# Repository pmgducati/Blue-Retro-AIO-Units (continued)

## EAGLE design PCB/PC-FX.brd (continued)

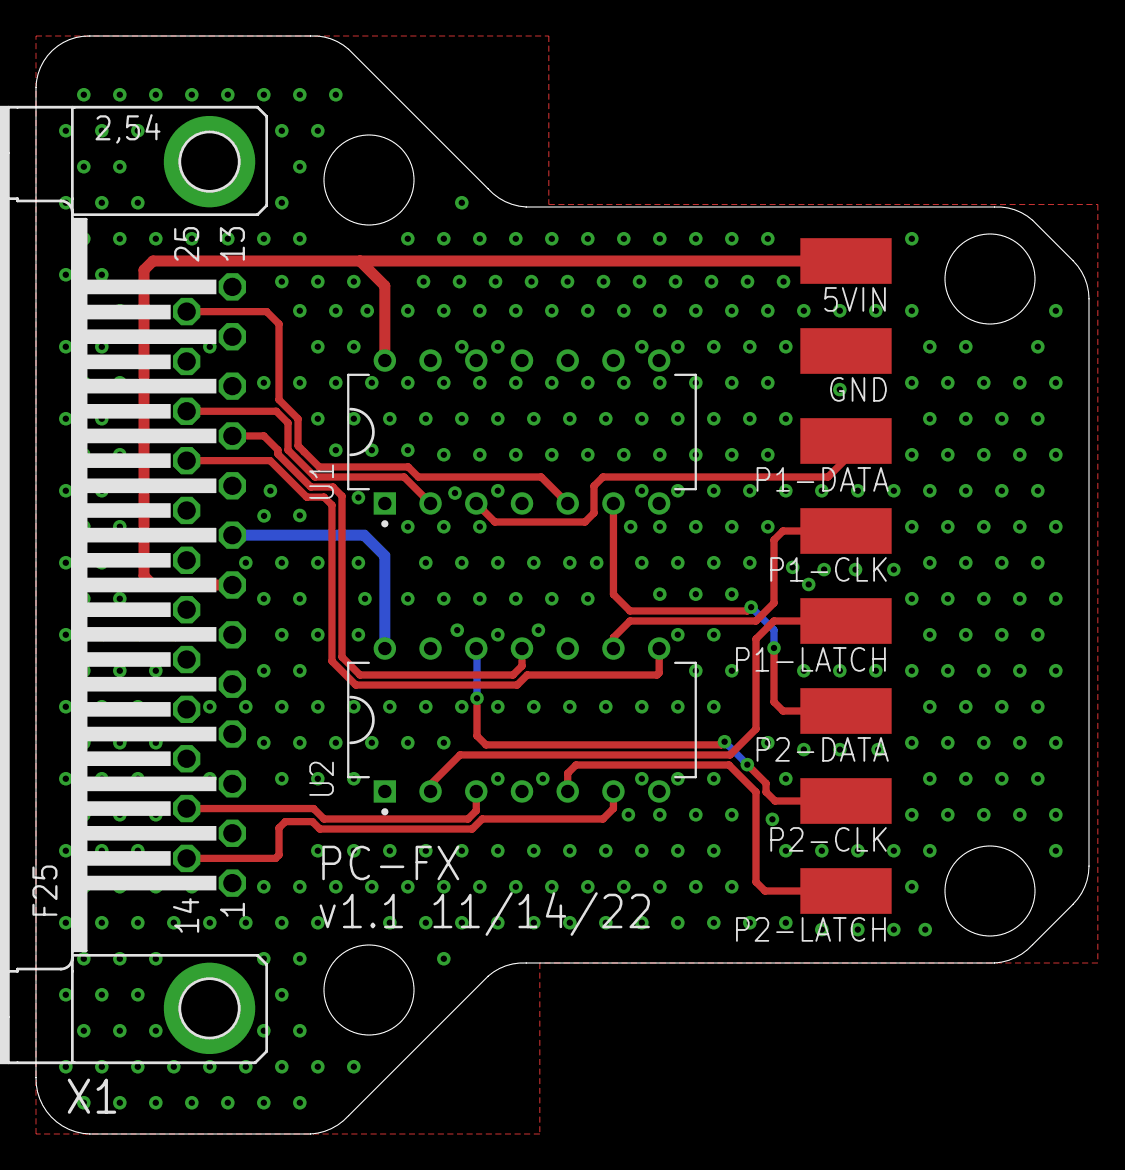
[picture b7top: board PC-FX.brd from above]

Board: 2 copper layers, 58.5 x 61.0 mm, 11 parts (0 on the bottom side), 15 nets.

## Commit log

2022-02-18 Initial Commit of all Files
2022-02-27 PCB Updates/New Additions
    All existing PCBs had silkscreen updates and NES, Virtual Boy, PSX/PS2, Nintendo 64, Saturn have been added.
2022-02-27 BOM Update
    Added extension Cable Links
2022-03-03 Clean Up
    Removing Uneeded Files
2022-03-03 Created Readme
2022-03-03 Clean Up Files
2022-03-14 Datasheets, BOM Update, 3 New PCBs
    Added Datasheets for the Female/Male DB25 connectors
    Updated formatting on the BOM
    New PCBs:
    Added Nintendo 64 (Updated to 1.1, Moved VIN from 5V to 3V3)
    Added Sega Saturn (Updated to 1.1, Added 5V and GND Pads on bottom for Second player pads to ease install)
    Added NES
2022-03-14 Working On Virtual Boy PCB
    Need to find/make a cable that is not prohibitively expensive to test.
2022-03-14 PCB for PSX/PS2
    Working on testing the PCB
2022-03-14 Housing for PCBs
    This will include the housing designs for the Main PCB and all Aux PCBs
2022-03-15 Housing Update
    Finishing housing shape, PCB Mounts, Venting, Branding and System Names. Snap fit and wire holes not started
2022-03-15 Controller Wire Holes and Player Markings
    Added Controller wire holes and player markings per system
2022-03-21 Preliminary CAD and STLs
    The CAD is finished and STL Created. I have ordered the Housings to make sure the snap fit will work as intended. Once I receive the housings and test them I will merge the branch if everything looks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
2022-03-21 BOM Update
    Updated ESP32 Link to model with correct footprint in BOM
2022-03-22 PS2 Power Pin Swap
    The PCB could not detect the correct system using the 8V from the PS2 to the 5VIN on the ESP. Moving to the 3V3 from the PS2 to 3V3IN on the ESP corrected the issue and the PCB not works as intended.
2022-03-23 Moving Files
    moved Flashing tool to Flashing Stuff Directory and added 1.4 FW from darthcloud
2022-03-23 Sharp Edge Fix for Shapeways
    The cutout for the DB25 connector on the top parts had a fillet applied to eliminate a sharp edge that would have caused printing problems.
2022-03-23 Updated Pad Name for 3V3 input
    Pad name was still listed as P1-4/P2-4 which is the 8V pin, The pads have been renamed and order updated on the PCB
2022-03-24 Power Pin addition
    After working with Darthcloud, it was revealed that some PS2 consoles have weak VIN on either the 8V or the 3V3. To make sure this PCB will work in either situation, I have added the 8V (Pad 3) pad b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
2022-04-02 PCB Update for better Housing Fit
    All the PCBs were updated for better housing fitment.
    Common Changes across all PCBs:
    1. All Aux PCBs are now the exact same size. (there was a .1mm-.5mm Variance previous)
    2. All Aux PCBs Mounting holes are in the same location (there was a .05mm-.1mm Variance previous)
    3. The DB25 has been moved 1.2mm close to the edge of the PCB for better connection when in the housing.
    PCB Specific Updates:
2022-04-02 Housing Update
    Widened the DB25 opening to allow male DB25 to fit over Female DB25 while in Housing, relocated PCB mounts to match PCB hole location in recent change.
2022-04-06 Added SNES PCB and Gerber
    Added SNES PCB and Gerber
2022-04-06 Add Dreamcast PCB and Gerber
    Add Dreamcast PCB and Gerber
2022-04-06 Removing Eagle Working Files
2022-04-06 Add NeoGeo PCBs
    Added Neogeo/Jamma/Supergun PCBs. Both OD and PP versions
2022-04-06 Add PC-FX
    Added PC-FX PCB Sch and Gerber
2022-04-06 Add CDi
    Added CDi PCB Schetmatic and gerber
2022-04-06 Add Jaguar
    Added Atari Jaguar PCB, Schematic and Gerber
2022-04-06 Add Sega Genesis
    Added Sega Genesis PCB, Schematic and Gerber
2022-04-06 Add Atari 2600 and SG-1000/SMS
    Added PCBs, Schematics and Gerbers for both PP and OD variants of the Atari 2600 and SG-1000/SMS (Both known as Parallel 2P)
2022-04-15 Housing Update and Font Add
    Changed female snap fit on the main housing bottom to overrun the main counterpart on both sides by .5mm (was 1mm)
    Updated STLs for Main Housing Bottom and all AUX Tops as this was not done on last commit.
    Added Font used for console logos
2022-04-15 Adding Project Status XLS
2022-04-16 TG-16
    Turbugrafx-16 Configuration is complete and Sega Genesis is in progress
2022-04-18 Added console variants to housing CAD and updated STLs
    Refreshed all Current STLs, Added 9 Variant AUX Covers to the Housing CAD
    New Variants Tops:
    Atari 2600, Atari 7800, Phillips CD-i, Famicom, Sega Genesis, Super Famicom, SNES, TurboGrafx 16 and Virtual Boy
2022-04-19 Added New Systems Housing Variants and supporting fonts
    Finished Housing Variants for Atari Jaguar, Dreamcast, Neo Geo, PC-FX, Sega Master System, Sega Mega Drive and SG-1000
    Gerbers for all files have been created and fonts used added to the fonts folder.
2022-04-19 Changed Player Order for N64 and Gamecube
    Reversed the player order of the pads on the PCB, when installing in the housing the controller wires would twist. this resolves that issue.
2022-04-20 Added Atari 7800 PCB and Gerber
    PCB was successfully able to be in the same footprint as all other variants. However it is the tightest design of all variants!
2022-04-20 Updated Project Status XLS
2022-04-20 Added Sega Genesis/Megadrive Multitap Support
    Added PCB/Gerber and Update SW CAD/ Added STLs for the Genesis/Megadrive Multitap version.
2022-04-20 JVS PCB
    Working on JVS PCB, need some clarification from Darthcloud on the Schematic Labels before proceeding
2022-04-27 BOM Update
    Updated BOM to include all recently added System components
2022-05-03 Naming Cleanup
    Changed Naming to be consistent between repos
2022-06-08 Fixed Omission of Main PCB in BOME PDF
    The print area was not correct in the XLS which then omitted the Main PCB. It has been updated.
2022-06-14 Update Project Status
    PC-FX functionality is confirmed, thanks to hipsofjw for testing it for me.
2022-06-14 CD-i PCB/BOM Update
    Identified USB Mini from Digikey and add it to the BOM.
    Updated the PCB to match the layout for the USB Mini Connector and added a callout on the PCB that the connector is required for 5V Power.
    Updated project status to include the complete PC-FX Status.
2022-06-14 Update BOM.pdf
    Added CD-i USB Mini connector
2022-06-15 CD-i Housing Update
    Added a opening in the housing for the usb power port and offset the controller cable hole to the side. Includes the solidworks files and STLs
2022-06-15 Adding P2 Controller Wire hole to Housing
2022-07-01 Adding Alternate Main PCB
    I added a alternate Main PCB that has a more standard (wider) ESP foorprint.
    The BOM has also been updated to include the Main ALT PCB
2022-07-01 Create Main - Wide ESP_2022-07-01.zip
    Forgot to add gerber for the alternate Main PCB in the last merge
2022-09-12 Updates from Issues 42/43/18
    Closed Issues 42 and 43 as Sega Genesis and PSX have been successfully tested and functional.
    Updated Dreamcast PCB per comment in Issue 18 - Reversed P1-P4 pads to match housing
    Updated Project Status to reflect #42 and #43 Complete
2022-09-12 Update README.md
    Updated Project Status
2022-11-14 Added exposed GND plane at DB25 anchors
    All PCBs have been update to have exposed GND plane pads for the DB25 anchor points.
    This resolves Issue 54
2022-11-14 Update BOM.xlsx
    Changed the Link for the Alt Wide Version to the correct 38 Pin version
2022-11-14 PCB Design
    Started design of Wii Ext & NES/SNES Mini PCBs
    I ordered the initial PCB and will update once I receive them
    Once the PCB is verified, I will work on the housing CAD
2022-11-14 Adding USB-C Datasheet and Library
2022-11-14 Update BOM.xlsx
    Added info for Wii Ext & SNES/NES Mini PCB components
2022-11-15 Retiring Main PCB
    Retiring Original Main PCB design as the unit is thinner that the standard footprint. This was causing confusion. The new main used to be Main Alt Wide version. It is now the standard as it fits the 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
2022-11-15 Adding FW 1.7.3 from Darthcloud
2022-11-16 Update README.md
    Updating Progress Chart
2022-11-28 Wii Ext, NES/SNES Mini PCB Design Status
    Design is complete, updating BOM and project Status before merging.
2022-11-28 Wii Ext, NES/SNES mini PCB design complete (#59)
    * PCB Design
    Started design of Wii Ext & NES/SNES Mini PCBs
    I ordered the initial PCB and will update once I receive them
    Once the PCB is verified, I will work on the housing CAD
    * Adding USB-C Datasheet and Library
    * Update README.md
2022-11-28 Update README.md
    Update Progress image
2022-11-29 CAD Update
    I have completed the preliminary CAD for the Wii EXT & NES/SNES Classic PCBs. I have ordered them from Shapeways and will merge the branch if no additional changes are needed.
    Included in this commit are the following:
    Updated CAD and STLs for the AUX housing Top for the NES Classic, SNES Classic, Famicom Classic, Super Famicom Classic, Wii Ext and Oprional Wii
    The Aux Bottom that covers all the variants mentioned above.
    As Always the CAD is included and the new font for the Wii Variants is included as well.
2022-11-29 Updated Housing color for renders
2022-11-29 Add Support for 5V PD Chargers
    Added 5.1K pull down resistors on the CC1 and CC2 to enable the use of a PD charger for 5V charging. Also cleaned up the PCB design and spread out pads for easier assembly.
2022-12-21 VB Housing and File House Keeping
    Created the housing for the Virtual Boy, added a 3D printable VB controller plug parts (Thanks RetroOnyx)
    Renamed all STLs with Console Company Names for consistency
    Updated the BOM for the Virtual Boy Parts and Added 3D Printed Parts for BOM also.
2022-12-28 Add Support for 5V PD Chargers (#61)
    Added 5.1K pull down resistors on the CC1 and CC2 to enable the use of a PD charger for 5V charging. Also cleaned up the PCB design and spread out pads for easier assembly.
2023-01-03 Updated Project Status
    Marking the new PCB and housing design complete
2023-01-03 Wii ext nes snes classic cad (#62)
    * CAD Update
    I have completed the preliminary CAD for the Wii EXT & NES/SNES Classic PCBs. I have ordered them from Shapeways and will merge the branch if no additional changes are needed.
    Included in this commit are the following:
    Updated CAD and STLs for the AUX housing Top for the NES Classic, SNES Classic, Famicom Classic, Super Famicom Classic, Wii Ext and Oprional Wii
    The Aux Bottom that covers all the variants mentioned above.
    As Always the CAD is included and the new font for the Wii Variants is included as well.
2023-01-09 Silkscreen Update, Library Add, Datasheet Add
    Updated the silkscreen on all PCBs that used the SN74 components as there was not orientation marker on the silkscreen.
    Added Modified SN74 libraries and VB Cable Pinout image
2023-03-20 Updated BOM for SNES Multitap Clarity
2023-03-20 Update README.md
    Update Project Status
2023-03-25 Silkscreen Change
    Added callout to connect cable shield to GND for PCB PCB. This fixes issues with the 6 button alternate config for the PCE
2023-03-25 Silkscreen Change (#65)
    Added callout to connect cable shield to GND for PCB PCB. This fixes issues with the 6 button alternate config for the PCE
2023-06-21 Update README.md (#68)
2023-11-28 Update README.md (#72)
2023-11-28 UPDATE GIT IGNORE
